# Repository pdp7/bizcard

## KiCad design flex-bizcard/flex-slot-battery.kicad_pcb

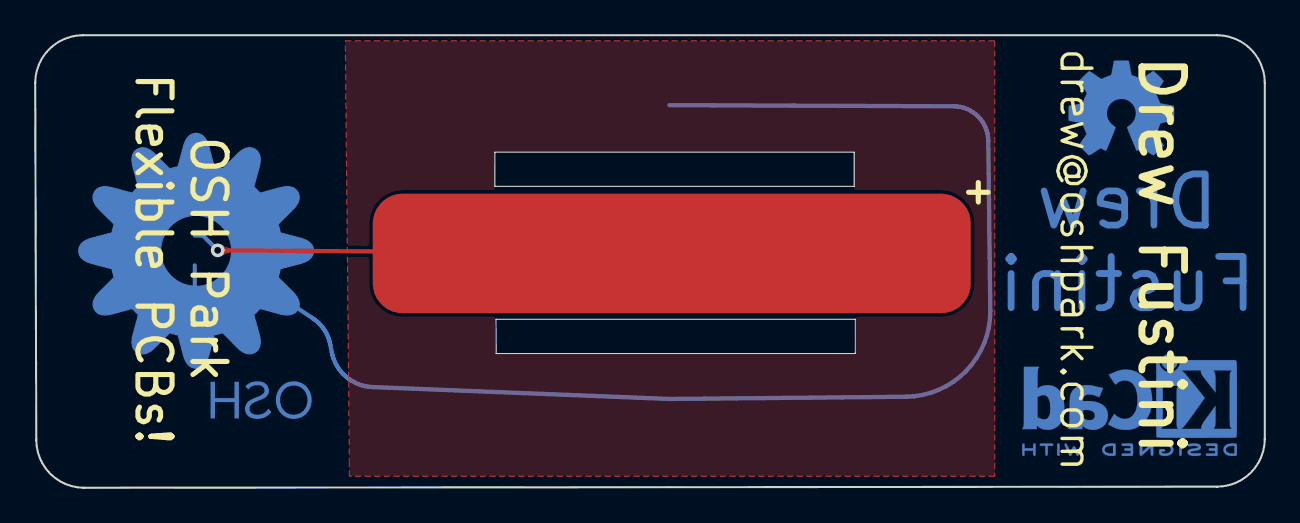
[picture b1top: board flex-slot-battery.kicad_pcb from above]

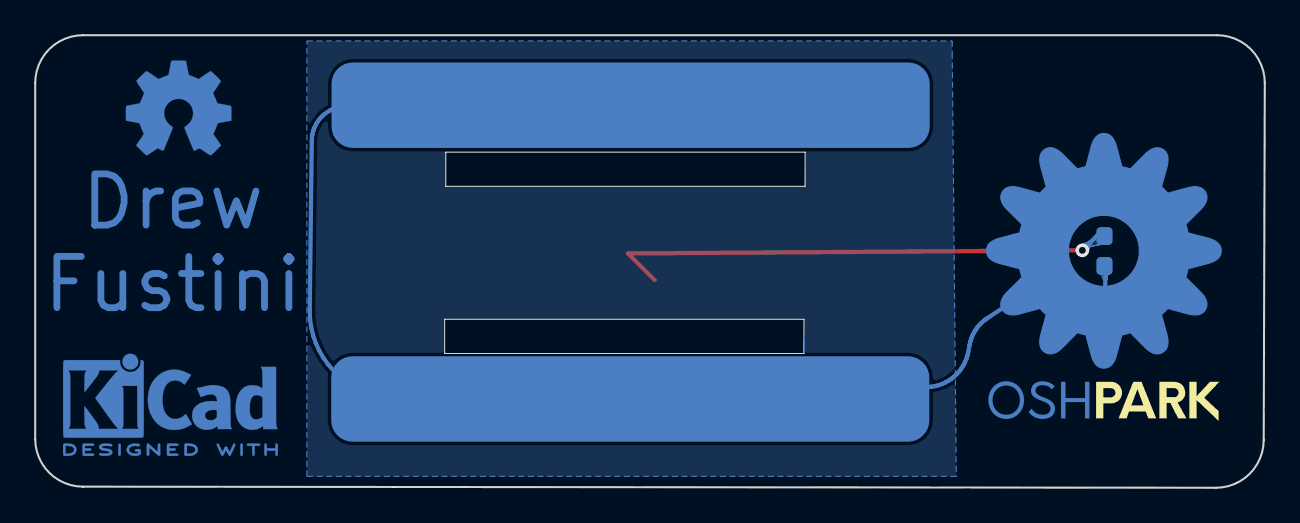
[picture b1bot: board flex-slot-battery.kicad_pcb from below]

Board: 2 copper layers, 71.9 x 26.5 mm, 5 parts (4 on the bottom side), 2 nets.

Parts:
D1: LED; LED_0603_1608Metric_Pad1.05x0.95mm_HandSolder-no-silk
J1: Conn_01x01_Female; coin-slot-pwr
J2, J3: Conn_01x01_Female; coin-slot-gnd
OSH_small: G***; OSH_small_copper-mask

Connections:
+3V3: D1.2, J1.1
GND: D1.1, J2.1, J3.1

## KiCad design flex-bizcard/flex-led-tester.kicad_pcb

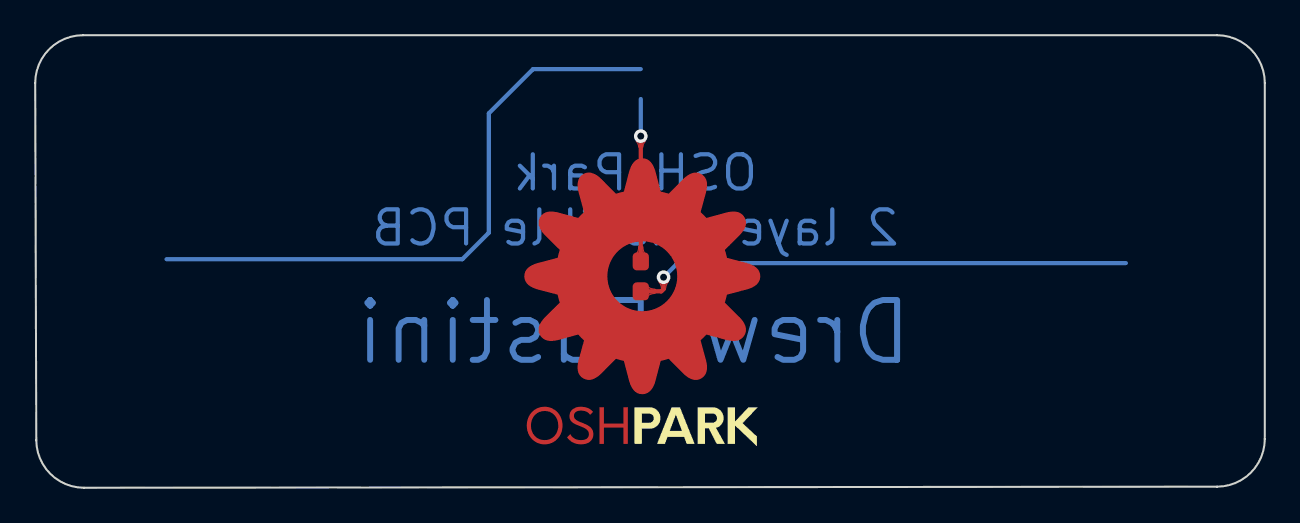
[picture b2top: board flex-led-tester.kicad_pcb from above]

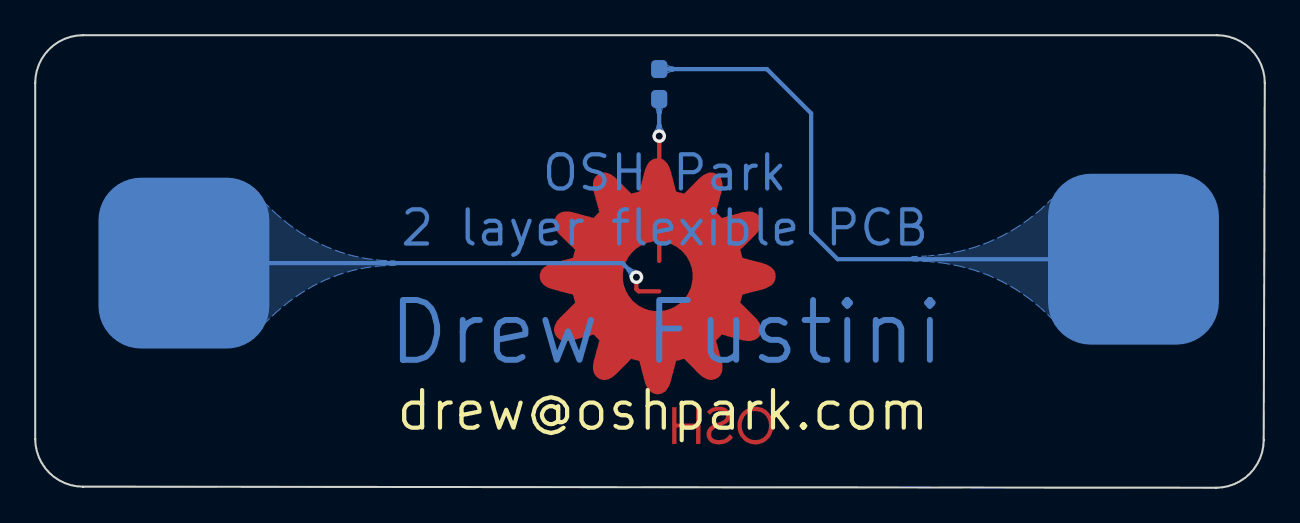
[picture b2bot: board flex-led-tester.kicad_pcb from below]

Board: 2 copper layers, 71.9 x 26.5 mm, 5 parts (3 on the bottom side), 3 nets.

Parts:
D1: LED; LED_0603_1608Metric_Pad1.05x0.95mm_HandSolder
J1, J2: Conn_01x01_Female; TestPoint_Pad_4.0x4.0mm
OSH_small: G***; OSH_small_copper-mask
R1: R; R_0603_1608Metric_Pad1.05x0.95mm_HandSolder

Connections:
+3V3: J1.1, R1.2
GND: D1.1, J2.1
unnamed: D1.2, R1.1

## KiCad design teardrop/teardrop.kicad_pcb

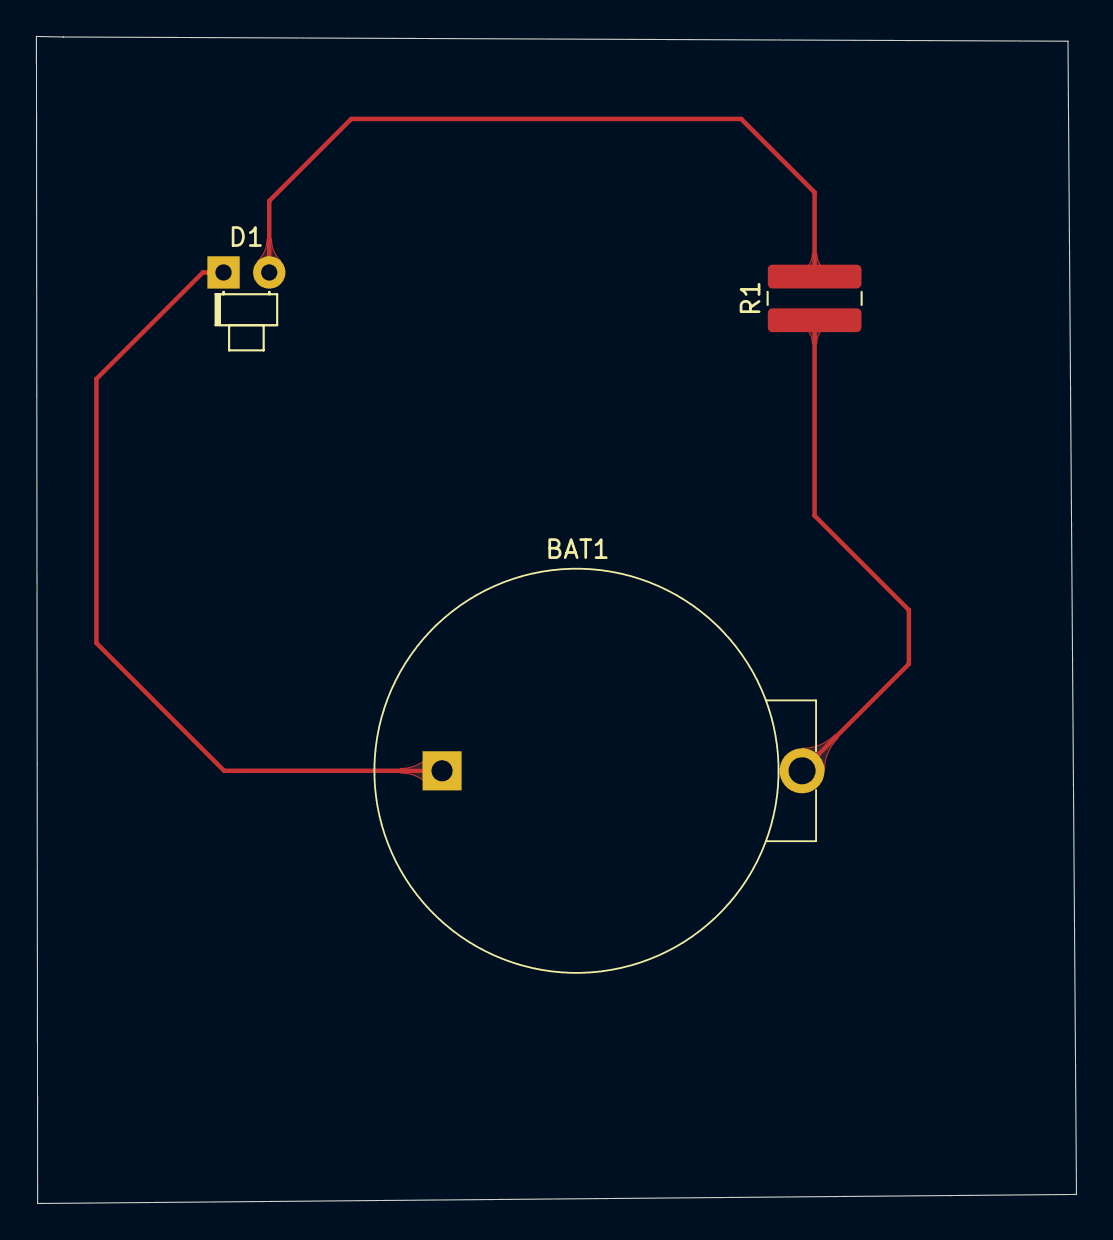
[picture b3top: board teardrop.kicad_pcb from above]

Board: 2 copper layers, 57.8 x 64.8 mm, 3 parts (0 on the bottom side), 3 nets.

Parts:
BAT1: BS-7; Battery_Holder_Coin_2032_BS-7
D1: LED; LED_D1.8mm_W1.8mm_H2.4mm_Horizontal_O1.27mm_Z1.6mm
R1: R; R_1020_2550Metric_Pad1.33x5.20mm_HandSolder

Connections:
unnamed: BAT1.Neg, D1.1
unnamed: BAT1.Pos, R1.1
unnamed: D1.2, R1.2

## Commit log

2019-12-03 add afterdark
2019-12-05 add new after dark biz card
2019-12-06 update flex and after dark biz cards
2019-12-09 update bizcard designs
2019-12-14 create schematic and relayout flex batt tester
    the teardrop plugin needs a schematic to work properly:
2019-12-17 improve teardrops on the flex LED tester
2019-12-17 Move text so that the via teardrop zones are filled
    for more information, refer to:
    https://github.com/NilujePerchut/kicad_scripts/issues/15#issuecomment-566487702
2019-12-18 most recent flex led tester
2019-12-20 make After Dark with no hole and SMD pads for power
2019-12-26 update flex biz card
2020-01-04 add after dark coincell bizcard design
2020-01-06 add flex coincell slot bizcard
2020-01-06 make flex LED tester with curved traces
2020-01-27 add polarity mark to flex coin slot
2020-01-28 removed resistor from afterdark bizcard
2020-01-28 add polarity marker to LED
2020-01-28 add 1206 LED variation
2020-01-29 make version with no resistor
2020-01-29 remove silk lines from LED footprint
2020-01-30 remove resistors
2020-02-13 add copper fill zone to flex slot bizcard
2020-02-18 add OHS20 flex strip
2020-02-21 update flex tester
